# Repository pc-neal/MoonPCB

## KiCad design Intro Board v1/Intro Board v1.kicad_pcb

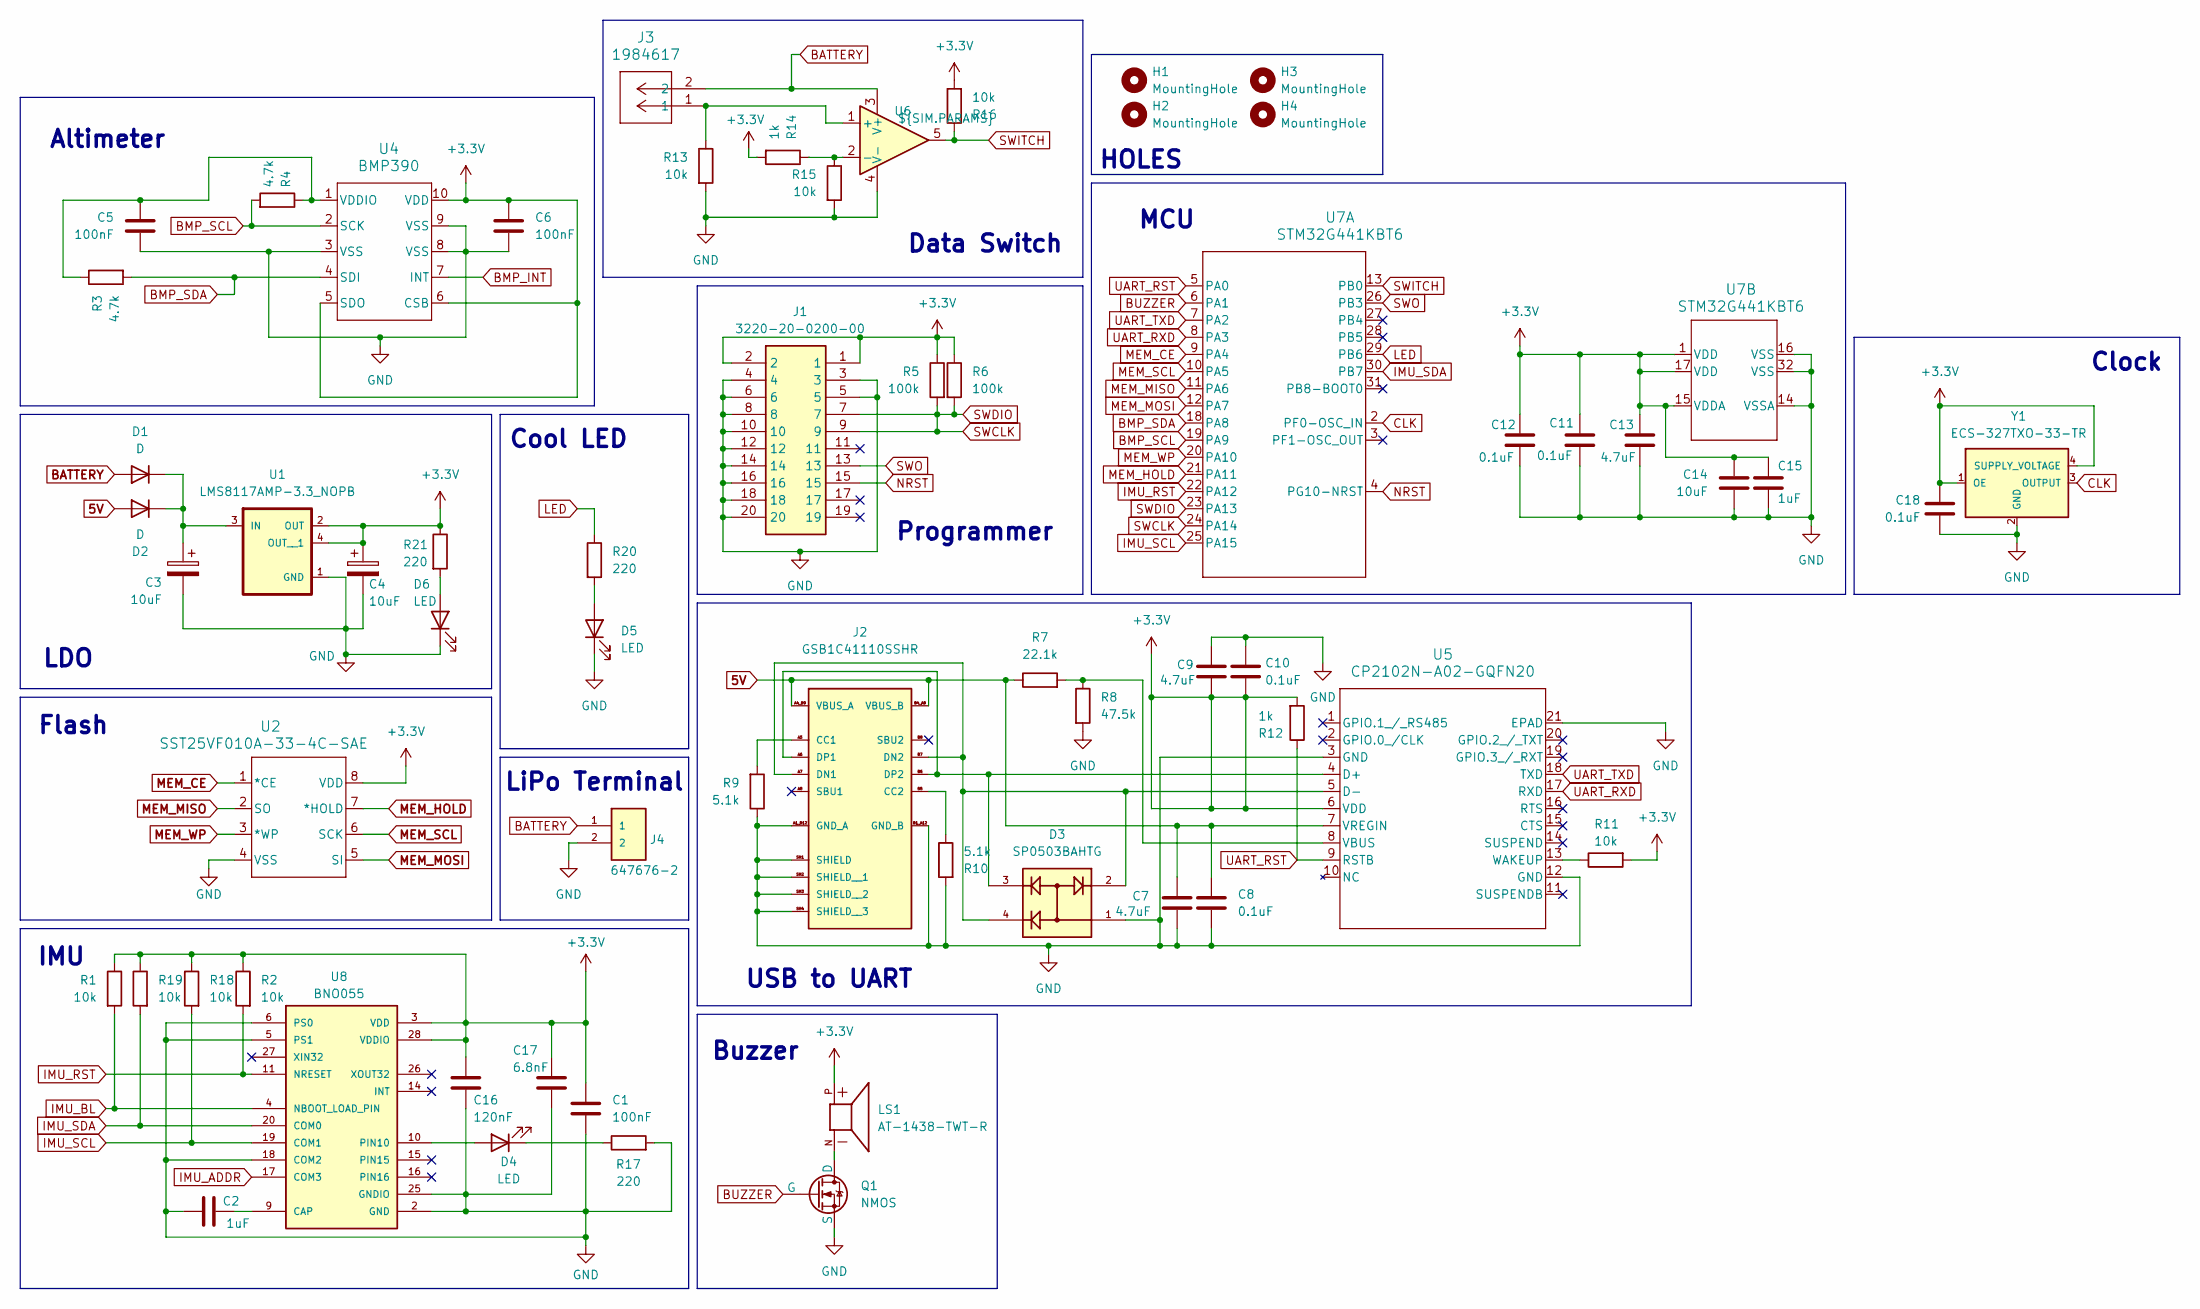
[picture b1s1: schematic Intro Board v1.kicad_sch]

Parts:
C1, C5, C6: 100nF; C_0603_1608Metric
C2, C15: 1uF; C_0603_1608Metric
C3, C4, C14: 10uF; C_0603_1608Metric
C7, C9, C13: 4.7uF; C_0603_1608Metric
C8, C10, C11, C12, C18: 0.1uF; C_0603_1608Metric
C16: 120nF; C_0603_1608Metric
C17: 6.8nF; C_0603_1608Metric
D1, D2: D; D_0603_1608Metric
D3: SP0503BAHTG; SOT143; PARTREV N/A
D4, D5, D6: LED; LED_0603_1608Metric
H1, H2, H3, H4: MountingHole; MountingHole_2.2mm_M2
J1: 3220-20-0200-00; 322020020000; Manufacturer_Part_Number 3220-20-0200-00
J2: GSB1C41110SSHR; AMPHENOL_GSB1C41110SSHR; PARTREV AX1
J3: 1984617; CONN_1984617_PXC
J4: 647676-2; TE_647676-2; PARTREV R
LS1: AT-1438-TWT-R; XDCR_AT-1438-TWT-R; PARTREV H
Q1: NMOS; TSOT-23
R1, R2, R11, R13, R15, R16, R18, R19: 10k; R_0603_1608Metric
R3, R4: 4.7k; R_0603_1608Metric
R5, R6: 100k; R_0603_1608Metric
R7: 22.1k; R_0603_1608Metric
R8: 47.5k; R_0603_1608Metric
R9, R10: 5.1k; R_0603_1608Metric
R12, R14: 1k; R_0603_1608Metric
R17, R20, R21: 220; R_0603_1608Metric
U1: LMS8117AMP-3.3_NOPB; SOT230P700X180-4N
U2: SST25VF010A-33-4C-SAE; SOIC8_SA_SST_MCH
U4: BMP390; 10LGA_2X2X0p75_BOS
U5: CP2102N-A02-GQFN20; QFN20_CP2102N_SIL
U6: ${SIM.PARAMS}; SOT-23-5_HandSoldering
U7: STM32G441KBT6; LQFP-32
U8: BNO055; LGA28R50P4X10_380X520X100
Y1: ECS-327TXO-33-TR; OSC_ECS-327TXO-33-TR; PARTREV Rev.2019

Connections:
5V: C7.1, C8.1, D2.2 (A), J2.A4_B9 (VBUS_A), J2.B4_A9 (VBUS_B), R7.1, U5.7 (VREGIN)
+3.3V: C1.1, C4.1, C6.1, C9.2, C10.2, C11.1, C12.1, C13.1, C14.1, C15.1, C16.1, C17.1, C18.1, J1.1, J1.2, LS1.P, R1.1, R2.1, R5.1, R6.1, R11.2, R12.2, R14.2, R16.2, R18.1, R19.1, R21.1, U1.2 (OUT), U1.4 (OUT__1), U2.8 (VDD), U4.5 (SDO), U4.6 (CSB), U4.10 (VDD), U5.6 (VDD), U7.1 (VDD), U7.15 (VDDA), U7.17 (VDD), U8.3 (VDD), U8.28 (VDDIO), Y1.1 (OE), Y1.4 (SUPPLY_VOLTAGE)
BATTERY: D1.2 (A), J3.2, J4.1, U6.3 (V+)
BMP_INT: U4.7 (INT)
BMP_SCL: R4.2, U4.2 (SCK), U7.19 (PA9)
BMP_SDA: R3.2, U4.4 (SDI), U7.18 (PA8)
BUZZER: Q1.2 (G), U7.6 (PA1)
CLK: U7.2 (PF0-OSC_IN), Y1.3 (OUTPUT)
GND: C1.2, C2.1, C3.2, C4.2, C5.2, C6.2, C7.2, C8.2, C9.1, C10.1, C11.2, C12.2, C13.2, C14.2, C15.2, C16.2, C17.2, C18.2, D3.1, D5.1 (K), D6.1 (K), J1.3, J1.4, J1.5, J1.6, J1.8, J1.10, J1.12, J1.14, J1.16, J1.18, J1.20, J2.A1_B12 (GND_A), J2.B1_A12 (GND_B), J2.SH1 (SHIELD), J2.SH2 (SHIELD__1), J2.SH3 (SHIELD__2), J2.SH4 (SHIELD__3), J4.2, Q1.3 (S), R8.2, R9.1, R10.2, R13.2, R15.2, R17.2, U1.1 (GND), U2.4 (VSS), U4.3 (VSS), U4.8 (VSS), U4.9 (VSS), U5.3 (GND), U5.12 (GND), U5.21 (EPAD), U6.4 (V-), U7.14 (VSSA), U7.16 (VSS), U7.32 (VSS), U8.2 (GND), U8.5 (PS1), U8.6 (PS0), U8.18 (COM2), U8.25 (GNDIO), Y1.2 (GND)
IMU_ADDR: U8.17 (COM3)
IMU_BL: R1.2, U8.4 (NBOOT_LOAD_PIN)
IMU_RST: R2.2, U7.22 (PA12), U8.11 (NRESET)
IMU_SCL: R18.2, U7.25 (PA15), U8.19 (COM1)
IMU_SDA: R19.2, U7.30 (PB7), U8.20 (COM0)
LED: R20.1, U7.29 (PB6)
MEM_CE: U2.1 (*CE), U7.9 (PA4)
MEM_HOLD: U2.7 (*HOLD), U7.21 (PA11)
MEM_MISO: U2.2 (SO), U7.11 (PA6)
MEM_MOSI: U2.5 (SI), U7.12 (PA7)
MEM_SCL: U2.6 (SCK), U7.10 (PA5)
MEM_WP: U2.3 (*WP), U7.20 (PA10)
NRST: J1.15, U7.4 (PG10-NRST)
unnamed: C3.1, D1.1 (K), D2.1 (K), U1.3 (IN)
unnamed: D4.2 (A), U8.10 (PIN10)
unnamed: D4.1 (K), R17.1
unnamed: D5.2 (A), R20.2
unnamed: D6.2 (A), R21.2
unnamed: J2.A5 (CC1), R9.2
unnamed: J2.B5 (CC2), R10.1
unnamed: D3.2, D3.4, J2.A7 (DN1), J2.B7 (DN2), U5.5 (D-)
unnamed: D3.3, J2.A6 (DP1), J2.B6 (DP2), U5.4 (D+)
unnamed: LS1.N, Q1.1 (D)
unnamed: C5.1, R3.1, R4.1, U4.1 (VDDIO)
unnamed: R7.2, R8.1, U5.8 (VBUS)
unnamed: R11.1, U5.13 (WAKEUP)
unnamed: J3.1, R13.1, U6.1 (+)
unnamed: R14.1, R15.1, U6.2 (-)
unnamed: C2.2, U8.9 (CAP)
SWCLK: J1.7, J1.9, R5.2, R6.2, U7.23 (PA13), U7.24 (PA14)
SWITCH: R16.1, U6.5, U7.13 (PB0)
SWO: J1.13, U7.26 (PB3)
UART_RST: R12.1, U5.9 (RSTB), U7.5 (PA0)
UART_RXD: U5.17 (RXD), U7.8 (PA3)
UART_TXD: U5.18 (TXD), U7.7 (PA2)

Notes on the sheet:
Clock
Programmer
Altimeter
Cool LED
Buzzer
LiPo Terminal
Flash
Data Switch
USB to UART
HOLES
IMU
MCU
LDO

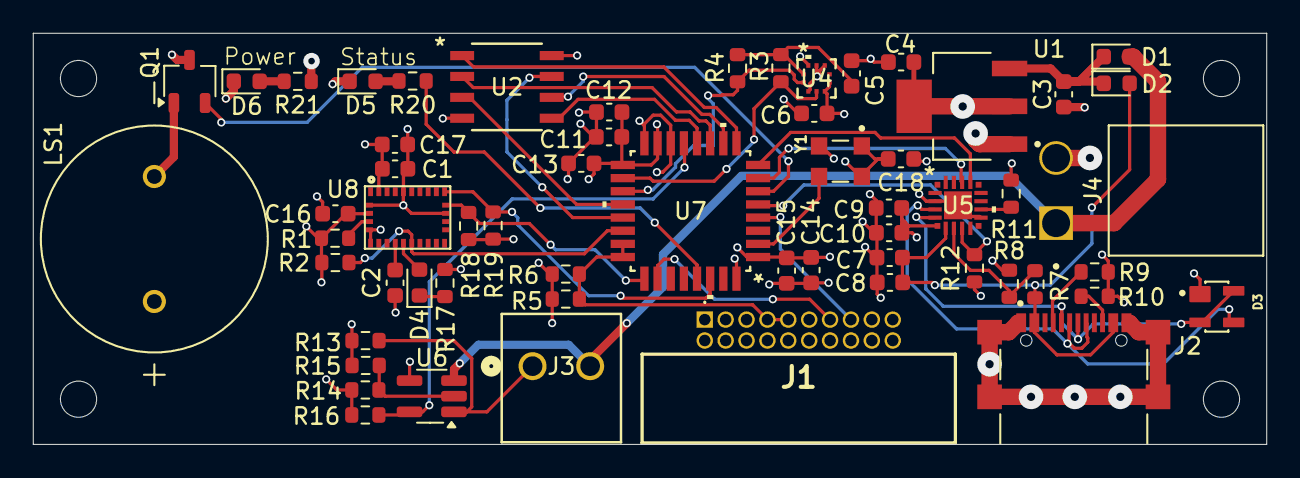
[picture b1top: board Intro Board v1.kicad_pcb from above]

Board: 4 copper layers, 75.0 x 25.0 mm, 63 parts (0 on the bottom side), 42 nets.

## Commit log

2026-02-13 PATRICK BOARD!!!!!
2026-02-13 PATRICK BOARD V2
2026-02-14 PATRICK BOARD V3
